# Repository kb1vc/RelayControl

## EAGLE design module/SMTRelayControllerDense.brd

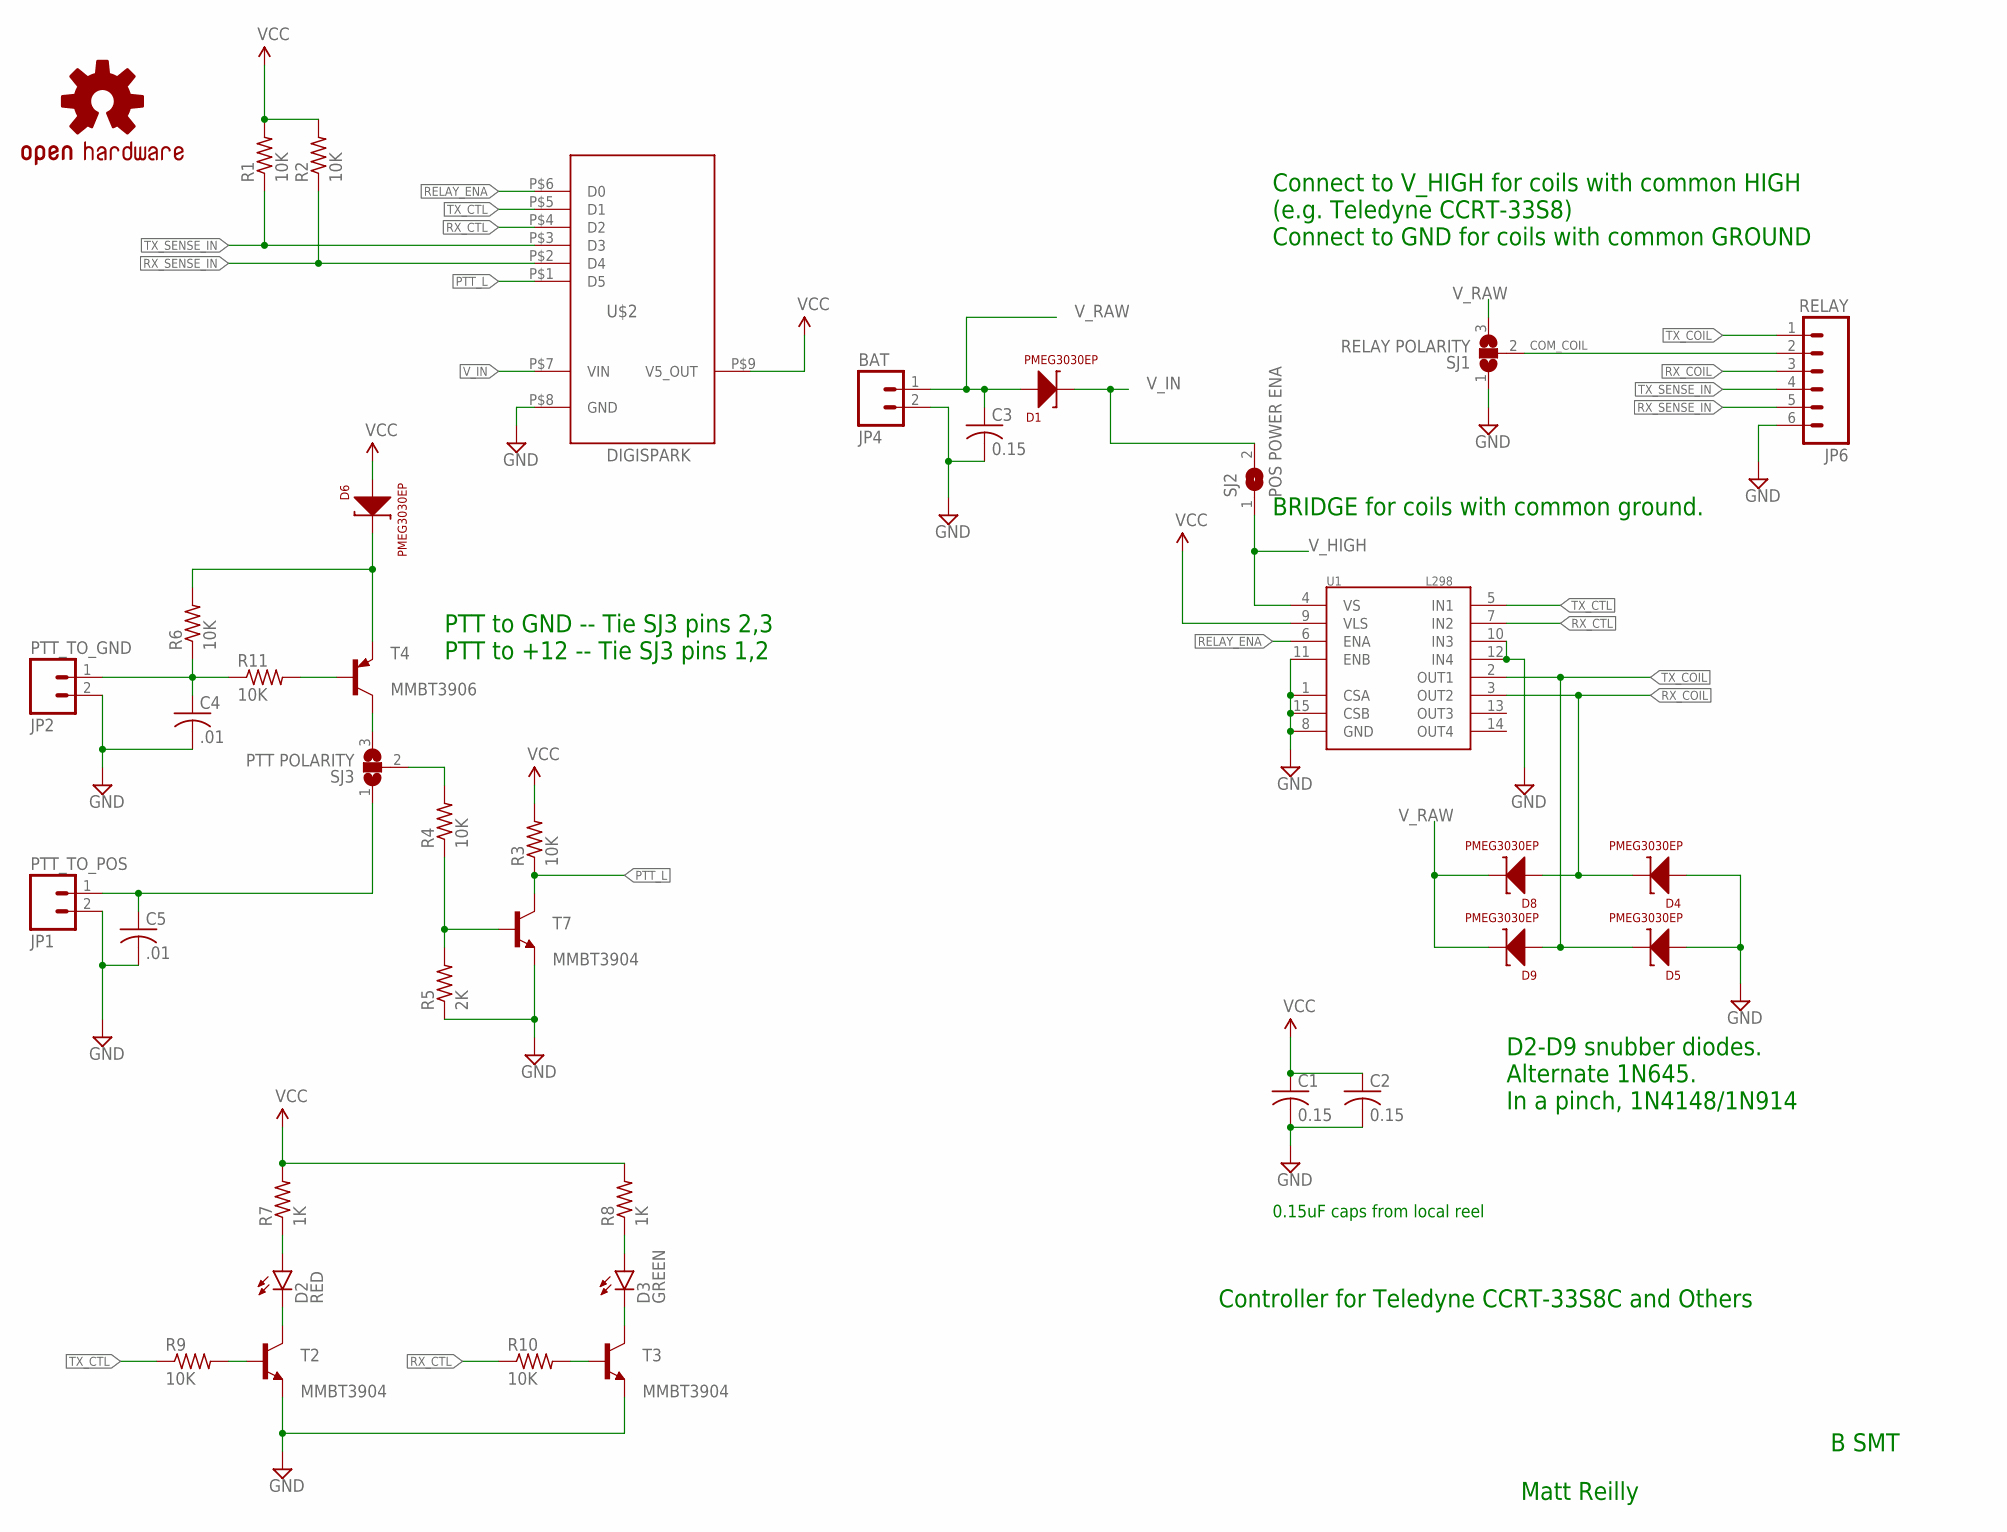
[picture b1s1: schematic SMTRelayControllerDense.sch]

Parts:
C1, C2, C3: 0.15; C1206K
C4, C5: .01; C1206K
D1, D4, D5, D6, D8, D9: PMEG3030EP; SOD128
D2: RED; LED-1206
D3: GREEN; LED-1206
JP1: PTT_TO_POS; SCREWTERMINAL-5MM-2
JP2: PTT_TO_GND; SCREWTERMINAL-5MM-2
JP4: BAT; SCREWTERMINAL-5MM-2
JP6: RELAY; MOLEX-1X6
LOGO2: OSHW-LOGOM; OSHW-LOGO-M
R1, R2, R3, R4, R6, R9, R10, R11: 10K; R1206
R5: 2K; R1206
R7, R8: 1K; R1206
SJ1: RELAY POLARITY; SJ_2W
SJ2: POS POWER ENA; SJW
SJ3: PTT POLARITY; SJ_2W
T2, T3, T7: MMBT3904; SOT23-BEC
T4: MMBT3906; SOT23-BEC
U1: L298; MULTIWATT15
U$2: DIGISPARK; DIGISPARK_FP

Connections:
COM_COIL: JP6.2, SJ1.2
GND: C1.2, C2.2, C3.2, C4.2, C5.2, D4.P$1 (A), D5.P$1 (A), JP1.2, JP2.2, JP4.2, JP6.6, R5.1, SJ1.1, T2.E, T3.E, T7.E, U1.1 (CSA), U1.8 (GND), U1.10 (IN3), U1.11 (ENB), U1.12 (IN4), U1.15 (CSB), U$2.P$8 (GND)
unnamed: C5.1, JP1.1, SJ3.1
unnamed: R4.2, SJ3.2
unnamed: D3.A, R8.1
unnamed: R4.1, R5.2, T7.B
unnamed: R11.2, T4.B
unnamed: D2.A, R7.1
unnamed: D2.C, T2.C
unnamed: D3.C, T3.C
unnamed: R9.2, T2.B
unnamed: R10.2, T3.B
unnamed: C4.1, JP2.1, R6.1, R11.1
unnamed: D6.P$2 (C), R6.2, T4.E
unnamed: SJ3.3, T4.C
PTT_L: R3.1, T7.C, U$2.P$1 (D5)
RELAY_ENA: U1.6 (ENA), U$2.P$6 (D0)
RX_COIL: D4.P$2 (C), D8.P$1 (A), JP6.3, U1.3 (OUT2)
RX_CTL: R10.1, U1.7 (IN2), U$2.P$4 (D2)
RX_SENSE_IN: JP6.5, R2.1, U$2.P$2 (D4)
TX_COIL: D5.P$2 (C), D9.P$1 (A), JP6.1, U1.2 (OUT1)
TX_CTL: R9.1, U1.5 (IN1), U$2.P$5 (D1)
TX_SENSE_IN: JP6.4, R1.1, U$2.P$3 (D3)
VCC: C1.1, C2.1, D6.P$1 (A), R1.2, R2.2, R3.2, R7.2, R8.2, U1.9 (VLS), U$2.P$9 (V5_OUT)
V_HIGH: SJ2.1, U1.4 (VS)
V_IN: D1.P$2 (C), SJ2.2, U$2.P$7 (VIN)
V_RAW: C3.1, D1.P$1 (A), D8.P$2 (C), D9.P$2 (C), JP4.1, SJ1.3

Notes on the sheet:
0.15uF caps from local reel
Matt Reilly
B SMT
D2-D9 snubber diodes. Alternate 1N645. In a pinch, 1N4148/1N914
BRIDGE for coils with common ground.
Connect to V_HIGH for coils with common HIGH (e.g. Teledyne CCRT-33S8) Connect to GND for coils with common GROUND
PTT to GND -- Tie SJ3 pins 2,3 PTT to +12 -- Tie SJ3 pins 1,2
Controller for Teledyne CCRT-33S8C and Others

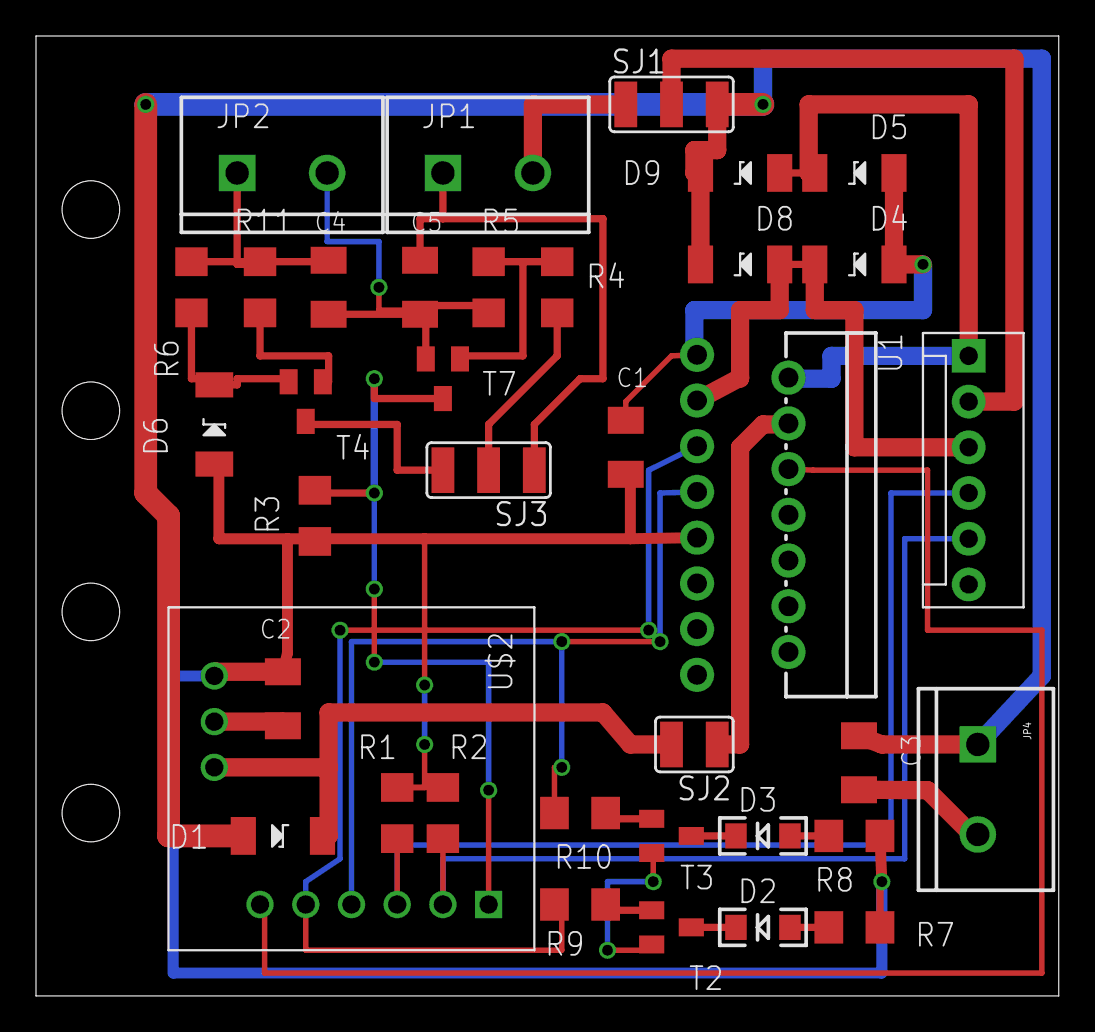
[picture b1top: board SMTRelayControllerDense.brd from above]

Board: 2 copper layers, 56.8 x 53.3 mm, 38 parts (1 on the bottom side), 27 nets.

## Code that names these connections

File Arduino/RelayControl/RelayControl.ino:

#define PTT_SENSE 5
#define TX_SENSE 4
#define TX_AN_SENSE 2
#define RX_SENSE 3
#define RX_AN_SENSE 3
#define TX_CTL 1
#define RX_CTL 2
#define RELAY_ENA 0


int PTT_state; 
int RX_now;
int Coil_is_on; 
int rx_sense; 
int tx_sense; 

void setup() {
  // put your setup code here, to run once:
  pinMode(PTT_SENSE, INPUT);
  pinMode(RX_SENSE, INPUT);
  pinMode(TX_SENSE, INPUT);
  digitalWrite(RX_SENSE, HIGH);
  digitalWrite(TX_SENSE, HIGH);
  pinMode(TX_CTL, OUTPUT);
  pinMode(RX_CTL, OUTPUT);
  pinMode(RELAY_ENA, OUTPUT);
  digitalWrite(RELAY_ENA, LOW);
  digitalWrite(TX_CTL, HIGH);
  digitalWrite(RX_CTL, LOW);
  RX_now = 0; 
  Coil_is_on = 0; 
} 

void loop() {
  // put your main code here, to run repeatedly:
  PTT_state = digitalRead(PTT_SENSE);
  if((PTT_state == LOW) && (RX_now == 1)) {
    // switch to TX mode. 
    RX_now = 0; 
    // energize the TX coil
    digitalWrite(RELAY_ENA, LOW); 
    digitalWrite(RX_CTL, HIGH); 
    digitalWrite(TX_CTL, LOW);  
     //   digitalWrite(RELAY_ENA, HIGH); 
  }
  else if((PTT_state == HIGH) && (RX_now == 0)) {
    // switch to RX mode
    RX_now = 1; 
    // energize the RX coil
    digitalWrite(RELAY_ENA, LOW); 
    digitalWrite(TX_CTL, HIGH); 
    digitalWrite(RX_CTL, LOW);
   //     digitalWrite(RELAY_ENA, HIGH); 
  }


  // now test the inputs and energize the appropriate coil
  // depending on what we're doing
  tx_sense = analogRead(TX_AN_SENSE); 
  rx_sense = analogRead(RX_AN_SENSE);
  
  if(RX_now == 1) {
    // we should be in RX mode.  test rx_sense
    if(rx_sense > 128) {
      // the relay hasn't closed yet.
      digitalWrite(RELAY_ENA, HIGH);
      delay(10);
    }
    else {
      digitalWrite(RELAY_ENA, LOW); 
    }
  }
  else {
    if(tx_sense > 128) {
      // the relay hasn't closed yet.
      digitalWrite(RELAY_ENA, HIGH);
      delay(10);
    }
    else {
      digitalWrite(RELAY_ENA, LOW); 
    }   
  }
}

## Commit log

2016-09-05 First commit -- proto released to OSHPARK
2016-09-05 added license file
2016-09-05 changed to CC BY SA 4.0 license
2016-09-15 Sketches work! Ready to test for the weekend!
2016-09-26 Updates with OSHW logo, surface mount parts, and improved PTT2GND (protected) circuit.
2019-08-17 saved dense schematic

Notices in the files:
module/SMTRelayControllerDense.brd:
See the license file at
https://creativecommons.org/licenses/by-sa/4.0
parts and their libraries:
SparkFun-LED: Licensing: Creative Commons ShareAlike 4.0 International - https://creativecommons.org/licenses/by-sa/4.0
